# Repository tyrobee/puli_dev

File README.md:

# puli_dev

s a simple dev board based of rp2040. It has everything that I would want on a dev board lots of GPIOs, plenty of grounds, and some other useful features (listed below). This was a fun and pretty easy project to make once I started to understand what I needed to do. It ended up being foundational to my ability to design PCBs, and it showed me how much I enjoy this kind of work. I hope I’ll be able to make even more dev boards later in life

# Features
1. The RP2040 is the brain of this project handling all of the processing
2. this uses the W25Q16JVZPIQ with a whopping 16-Megabit flash menmory
3. Usbc this is just a normal USB-C Receptical to send data and also power 
4. one pin for 5v power and another pin for 3v power 
5. 9 pins for ground to make it easy to ground everything you need to 
6. this board comes wih 29 gpio pins 4 of which are dual use for analog inputs (ADC pins)
7. also on this board is an led to make it easy to check if the board is powered on od if there any any problems also to help debug or even program
8. and finaly a button to enter into BOOTSEL mode so you can program you board.

# schematic

# PCB Layout

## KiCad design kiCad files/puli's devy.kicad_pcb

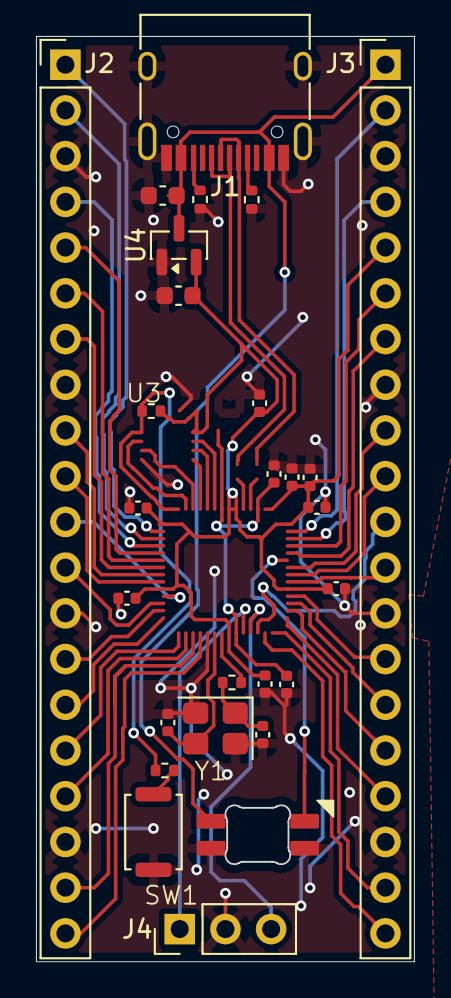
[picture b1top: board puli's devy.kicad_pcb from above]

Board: 2 copper layers, 21.0 x 51.4 mm, 27 parts (1 on the bottom side), 12 nets.

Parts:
C1, C10: 1uF; C_0402_1005Metric
C3, C4, C5, C6, C7, C8, C9, C12: 0.1uF; C_0402_1005Metric
C13, C14: 10uF; C_0603_1608Metric
C15, C16: 33pF; C_0402_1005Metric
D1: SK6812MINI; MX_SK6812MINI-E
J1: USB_C_Receptacle_USB2.0_14P; USB_C_Receptacle_HRO_TYPE-C-31-M-12
J2, J3: Conn_01x20; PinHeader_1x20_P2.54mm_Vertical
J4: Conn_01x03; PinHeader_1x03_P2.54mm_Vertical
R1, R2: 5.1k; R_0402_1005Metric
R5, R6: 1K; R_0402_1005Metric
R7: 10K; R_0402_1005Metric
SW1: SW_Push; SW_Push_SPST_NO_Alps_SKRK
U4: MCP1700x-330xxTT; SOT-23
Y1: 12 MHz; Crystal_SMD_3225-4Pin_3.2x2.5mm

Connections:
+1V1: C10.1, C12.1
+3V3: C1.1, C3.1, C4.1, C5.1, C6.1, C7.1, C8.1, C9.1, C14.1, J3.5, R7.2, U4.2 (VO)
GND: C1.2, C3.2, C4.2, C5.2, C6.2, C7.2, C8.2, C9.2, C10.2, C12.2, C13.2, C14.2, C15.1, C16.1, D1.1 (DOUT), D1.2 (VSS), J1.A1 (GND), J1.A12 (GND), J1.B1 (GND), J1.B12 (GND), J1.S1 (SHIELD), J2.3, J2.8, J2.13, J2.18, J3.3, J3.8, J3.13, J3.18, J4.2, R1.2, R2.2, SW1.1, U4.1 (GND), Y1.2, Y1.4
unnamed: C16.2, R5.1, Y1.1
unnamed: J1.A5 (CC1), R1.1
unnamed: J1.B5 (CC2), R2.1
unnamed: R6.1, SW1.2
QSPI_SS: R6.2, R7.1
USB_D+: J1.A6 (D+), J1.B6 (D+)
USB_D-: J1.A7 (D-), J1.B7 (D-)
VBUS: C13.1, D1.4 (VDD), J1.A4 (VBUS), J1.A9 (VBUS), J1.B4 (VBUS), J1.B9 (VBUS), J3.1, U4.3 (VI)
XIN: C15.2, Y1.3

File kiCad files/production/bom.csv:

Designator,Footprint,Quantity,Value,LCSC Part #
"C1, C10",0402,2,1uF,
"C12, C3, C4, C5, C6, C7, C8, C9",0402,8,0.1uF,
"C13, C14",0603,2,10uF,
"C15, C16",0402,2,33pF,
D1,MX_SK6812MINI-E,1,SK6812MINI,
J1,USB_C_Receptacle_HRO_TYPE-C-31-M-12,1,USB_C_Receptacle_USB2.0_14P,
"J2, J3",PinHeader_1x20_P2.54mm_Vertical,2,Conn_01x20,
J4,PinHeader_1x03_P2.54mm_Vertical,1,Conn_01x03,
"R1, R2",0402,2,5.1k,
"R5, R6",0402,2,1K,
R7,0402,1,10K,
SW1,SW_Push_SPST_NO_Alps_SKRK,1,SW_Push,
U4,SOT-23,1,MCP1700x-330xxTT,
Y1,Crystal_SMD_3225-4Pin_3.2x2.5mm,1,12 MHz,
